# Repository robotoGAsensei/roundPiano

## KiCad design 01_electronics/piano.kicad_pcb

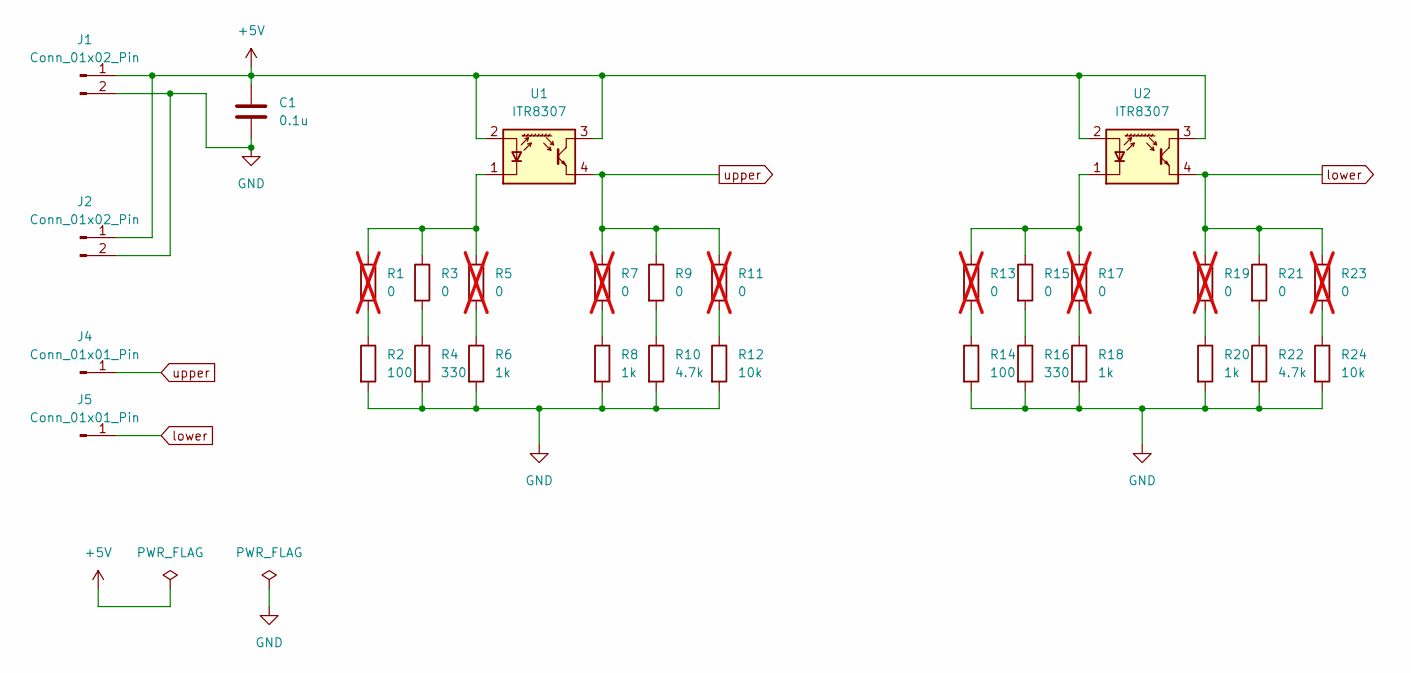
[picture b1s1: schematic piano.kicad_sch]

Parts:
C1: 0.1u; C_0603_1608Metric; LCSC C14663
J1, J2: Conn_01x02_Pin; con_pad_2
J4, J5: Conn_01x01_Pin; con_pad_1
R1, R5, R7, R11, R13, R17, R19, R23: 0; R_0603_1608Metric; not fitted
R2, R14: 100; R_0603_1608Metric; LCSC C22775
R3, R9, R15, R21: 0; R_0603_1608Metric; LCSC C21189
R4, R16: 330; R_0603_1608Metric; LCSC C23138
R6, R8, R18, R20: 1k; R_0603_1608Metric; LCSC C21190
R10, R22: 4.7k; R_0603_1608Metric; LCSC C23162
R12, R24: 10k; R_0603_1608Metric; LCSC C25804
U1, U2: ITR8307; Everlight_ITR8307; LCSC C81632

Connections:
+5V: C1.1, J1.1, J2.1, U1.2 (A), U1.3 (C), U2.2 (A), U2.3 (C)
GND: C1.2, J1.2, J2.2, R2.2, R4.2, R6.2, R8.2, R10.2, R12.2, R14.2, R16.2, R18.2, R20.2, R22.2, R24.2
unnamed: R1.2, R2.1
unnamed: R3.2, R4.1
unnamed: R5.2, R6.1
unnamed: R7.2, R8.1
unnamed: R9.2, R10.1
unnamed: R11.2, R12.1
unnamed: R13.2, R14.1
unnamed: R15.2, R16.1
unnamed: R17.2, R18.1
unnamed: R19.2, R20.1
unnamed: R21.2, R22.1
unnamed: R23.2, R24.1
unnamed: R1.1, R3.1, R5.1, U1.1 (K)
unnamed: R13.1, R15.1, R17.1, U2.1 (K)
lower: J5.1, R19.1, R21.1, R23.1, U2.4 (E)
upper: J4.1, R7.1, R9.1, R11.1, U1.4 (E)

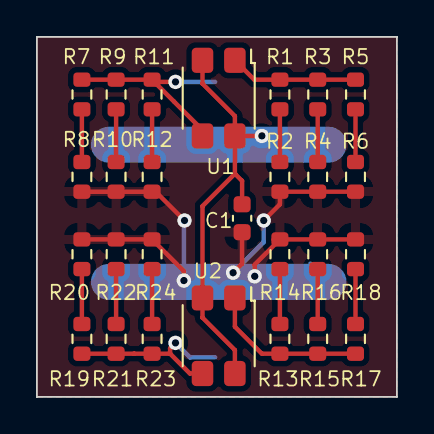
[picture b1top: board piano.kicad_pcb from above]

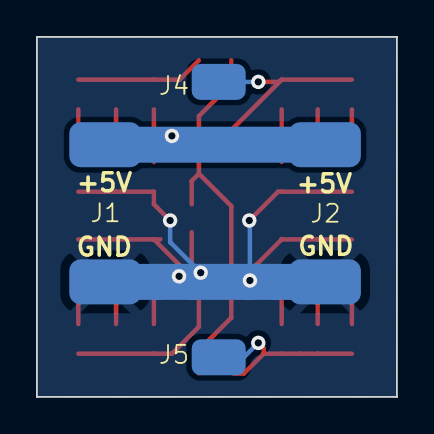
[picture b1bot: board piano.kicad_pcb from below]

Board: 2 copper layers, 20.0 x 20.0 mm, 31 parts (4 on the bottom side), 18 nets.

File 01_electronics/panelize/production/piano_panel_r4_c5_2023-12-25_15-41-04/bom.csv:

Designator,Footprint,Quantity,Value,LCSC Part #
"C1_20, C1_19, C1_18, C1_17, C1_16, C1_15, C1_14, C1_13, C1_12, C1_11, C1_10, C1_9, C1_8, C1_7, C1_6, C1_5, C1_4, C1_3, C1_2, C1",603,20,0.1u,C14663
"R10_20, R10_19, R10_18, R10_17, R10_16, R10_15, R10_14, R10_13, R10_12, R10_11, R10_10, R10_9, R10_8, R10_7, R10_6, R10_5, R10_4, R10_3, R10_2, R10, R22_20, R22_19, R22_18, R22_17, R22_16, R22_15, R22_14, R22_13, R22_12, R22_11, R22_10, R22_9, R22_8, R22_7, R22_6, R22_5, R22_4, R22_3, R22_2, R22",603,40,4.7k,C23162
"R12_20, R12_19, R12_18, R12_17, R12_16, R12_15, R12_14, R12_13, R12_12, R12_11, R12_10, R12_9, R12_8, R12_7, R12_6, R12_5, R12_4, R12_3, R12_2, R12, R24_20, R24_19, R24_18, R24_17, R24_16, R24_15, R24_14, R24_13, R24_12, R24_11, R24_10, R24_9, R24_8, R24_7, R24_6, R24_5, R24_4, R24_3, R24_2, R24",603,40,10k,C25804
"R14_20, R14_19, R14_18, R14_17, R14_16, R14_15, R14_14, R14_13, R14_12, R14_11, R14_10, R14_9, R14_8, R14_7, R14_6, R14_5, R14_4, R14_3, R14_2, R14, R2_20, R2_19, R2_18, R2_17, R2_16, R2_15, R2_14, R2_13, R2_12, R2_11, R2_10, R2_9, R2_8, R2_7, R2_6, R2_5, R2_4, R2_3, R2_2, R2",603,40,100,C22775
"R15_20, R15_19, R15_18, R15_17, R15_16, R15_15, R15_14, R15_13, R15_12, R15_11, R15_10, R15_9, R15_8, R15_7, R15_6, R15_5, R15_4, R15_3, R15_2, R15, R21_20, R21_19, R21_18, R21_17, R21_16, R21_15, R21_14, R21_13, R21_12, R21_11, R21_10, R21_9, R21_8, R21_7, R21_6, R21_5, R21_4, R21_3, R21_2, R21, R3_20, R3_19, R3_18, R3_17, R3_16, R3_15, R3_14, R3_13, R3_12, R3_11, R3_10, R3_9, R3_8, R3_7, R3_6, R3_5, R3_4, R3_3, R3_2, R3, R9_20, R9_19, R9_18, R9_17, R9_16, R9_15, R9_14, R9_13, R9_12, R9_11, R9_10, R9_9, R9_8, R9_7, R9_6, R9_5, R9_4, R9_3, R9_2, R9",603,80,0,C21189
"R16_20, R16_19, R16_18, R16_17, R16_16, R16_15, R16_14, R16_13, R16_12, R16_11, R16_10, R16_9, R16_8, R16_7, R16_6, R16_5, R16_4, R16_3, R16_2, R16, R4_20, R4_19, R4_18, R4_17, R4_16, R4_15, R4_14, R4_13, R4_12, R4_11, R4_10, R4_9, R4_8, R4_7, R4_6, R4_5, R4_4, R4_3, R4_2, R4",603,40,330,C23138
"R18_20, R18_19, R18_18, R18_17, R18_16, R18_15, R18_14, R18_13, R18_12, R18_11, R18_10, R18_9, R18_8, R18_7, R18_6, R18_5, R18_4, R18_3, R18_2, R18, R20_20, R20_19, R20_18, R20_17, R20_16, R20_15, R20_14, R20_13, R20_12, R20_11, R20_10, R20_9, R20_8, R20_7, R20_6, R20_5, R20_4, R20_3, R20_2, R20, R6_20, R6_19, R6_18, R6_17, R6_16, R6_15, R6_14, R6_13, R6_12, R6_11, R6_10, R6_9, R6_8, R6_7, R6_6, R6_5, R6_4, R6_3, R6_2, R6, R8_20, R8_19, R8_18, R8_17, R8_16, R8_15, R8_14, R8_13, R8_12, R8_11, R8_10, R8_9, R8_8, R8_7, R8_6, R8_5, R8_4, R8_3, R8_2, R8",603,80,1k,C21190
"U1_20, U1_19, U1_18, U1_17, U1_16, U1_15, U1_14, U1_13, U1_12, U1_11, U1_10, U1_9, U1_8, U1_7, U1_6, U1_5, U1_4, U1_3, U1_2, U1, U2_20, U2_19, U2_18, U2_17, U2_16, U2_15, U2_14, U2_13, U2_12, U2_11, U2_10, U2_9, U2_8, U2_7, U2_6, U2_5, U2_4, U2_3, U2_2, U2",Everlight_ITR8307,40,ITR8307,C81632

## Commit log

2024-02-07 move files so that it matches Arduino compiling requirements
2024-02-18 add function of lower contact when upper contacnt doesn't work well
2024-02-18 add modules for dac
2024-02-20 fix wrong channel assign to multiplexer
2024-02-21 remove unnecessary code
2024-02-22 fix wrong settings
2024-02-22 isolate high frequency task
2024-02-23 successfully made sound
2024-03-17 MakerFairKariya
2024-03-18 debug and refactor
2024-03-18 refactor, apply clang-format
2024-03-18 refactor, split multiplexer related code from Main
2024-03-20 feature, stop using DAC and use PWM instead
2024-03-22 feature, confirmed to make clear sound, add variables to monitor activation cycle
2024-03-22 refactor
2024-03-22 feature, fix periodic impulse noise made by bit mask of time_count
2024-03-22 feature, fix loundness calculation
